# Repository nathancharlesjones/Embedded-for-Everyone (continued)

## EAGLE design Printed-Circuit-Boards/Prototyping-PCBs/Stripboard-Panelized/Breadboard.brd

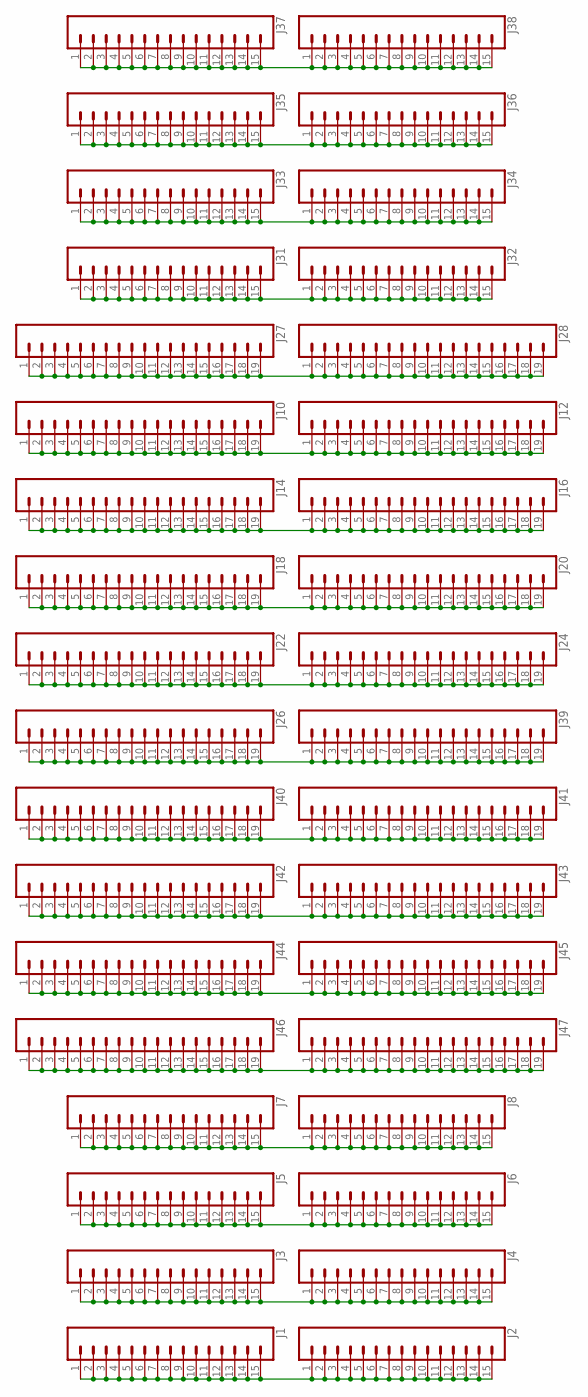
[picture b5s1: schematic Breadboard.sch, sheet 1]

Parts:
J1, J2, J3, J4, J5, J6, J7, J8, J31, J32, J33, J34, J35, J36, J37, J38: CONN_15; 1X15
J10, J12, J14, J16, J18, J20, J22, J24, J26, J27, J28, J39, J40, J41, J42, J43, J44, J45, J46, J47: CONN_19; 1X19

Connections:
unnamed: J37.1, J37.2, J37.3, J37.4, J37.5, J37.6, J37.7, J37.8, J37.9, J37.10, J37.11, J37.12, J37.13, J37.14, J37.15, J38.1, J38.2, J38.3, J38.4, J38.5, J38.6, J38.7, J38.8, J38.9, J38.10, J38.11, J38.12, J38.13, J38.14, J38.15
unnamed: J35.1, J35.2, J35.3, J35.4, J35.5, J35.6, J35.7, J35.8, J35.9, J35.10, J35.11, J35.12, J35.13, J35.14, J35.15, J36.1, J36.2, J36.3, J36.4, J36.5, J36.6, J36.7, J36.8, J36.9, J36.10, J36.11, J36.12, J36.13, J36.14, J36.15
unnamed: J33.1, J33.2, J33.3, J33.4, J33.5, J33.6, J33.7, J33.8, J33.9, J33.10, J33.11, J33.12, J33.13, J33.14, J33.15, J34.1, J34.2, J34.3, J34.4, J34.5, J34.6, J34.7, J34.8, J34.9, J34.10, J34.11, J34.12, J34.13, J34.14, J34.15
unnamed: J31.1, J31.2, J31.3, J31.4, J31.5, J31.6, J31.7, J31.8, J31.9, J31.10, J31.11, J31.12, J31.13, J31.14, J31.15, J32.1, J32.2, J32.3, J32.4, J32.5, J32.6, J32.7, J32.8, J32.9, J32.10, J32.11, J32.12, J32.13, J32.14, J32.15
unnamed: J27.1, J27.2, J27.3, J27.4, J27.5, J27.6, J27.7, J27.8, J27.9, J27.10, J27.11, J27.12, J27.13, J27.14, J27.15, J27.16, J27.17, J27.18, J27.19, J28.1, J28.2, J28.3, J28.4, J28.5, J28.6, J28.7, J28.8, J28.9, J28.10, J28.11, J28.12, J28.13, J28.14, J28.15, J28.16, J28.17, J28.18, J28.19
unnamed: J10.1, J10.2, J10.3, J10.4, J10.5, J10.6, J10.7, J10.8, J10.9, J10.10, J10.11, J10.12, J10.13, J10.14, J10.15, J10.16, J10.17, J10.18, J10.19, J12.1, J12.2, J12.3, J12.4, J12.5, J12.6, J12.7, J12.8, J12.9, J12.10, J12.11, J12.12, J12.13, J12.14, J12.15, J12.16, J12.17, J12.18, J12.19
unnamed: J14.1, J14.2, J14.3, J14.4, J14.5, J14.6, J14.7, J14.8, J14.9, J14.10, J14.11, J14.12, J14.13, J14.14, J14.15, J14.16, J14.17, J14.18, J14.19, J16.1, J16.2, J16.3, J16.4, J16.5, J16.6, J16.7, J16.8, J16.9, J16.10, J16.11, J16.12, J16.13, J16.14, J16.15, J16.16, J16.17, J16.18, J16.19
unnamed: J18.1, J18.2, J18.3, J18.4, J18.5, J18.6, J18.7, J18.8, J18.9, J18.10, J18.11, J18.12, J18.13, J18.14, J18.15, J18.16, J18.17, J18.18, J18.19, J20.1, J20.2, J20.3, J20.4, J20.5, J20.6, J20.7, J20.8, J20.9, J20.10, J20.11, J20.12, J20.13, J20.14, J20.15, J20.16, J20.17, J20.18, J20.19
unnamed: J22.1, J22.2, J22.3, J22.4, J22.5, J22.6, J22.7, J22.8, J22.9, J22.10, J22.11, J22.12, J22.13, J22.14, J22.15, J22.16, J22.17, J22.18, J22.19, J24.1, J24.2, J24.3, J24.4, J24.5, J24.6, J24.7, J24.8, J24.9, J24.10, J24.11, J24.12, J24.13, J24.14, J24.15, J24.16, J24.17, J24.18, J24.19
unnamed: J26.1, J26.2, J26.3, J26.4, J26.5, J26.6, J26.7, J26.8, J26.9, J26.10, J26.11, J26.12, J26.13, J26.14, J26.15, J26.16, J26.17, J26.18, J26.19, J39.1, J39.2, J39.3, J39.4, J39.5, J39.6, J39.7, J39.8, J39.9, J39.10, J39.11, J39.12, J39.13, J39.14, J39.15, J39.16, J39.17, J39.18, J39.19
unnamed: J40.1, J40.2, J40.3, J40.4, J40.5, J40.6, J40.7, J40.8, J40.9, J40.10, J40.11, J40.12, J40.13, J40.14, J40.15, J40.16, J40.17, J40.18, J40.19, J41.1, J41.2, J41.3, J41.4, J41.5, J41.6, J41.7, J41.8, J41.9, J41.10, J41.11, J41.12, J41.13, J41.14, J41.15, J41.16, J41.17, J41.18, J41.19
unnamed: J42.1, J42.2, J42.3, J42.4, J42.5, J42.6, J42.7, J42.8, J42.9, J42.10, J42.11, J42.12, J42.13, J42.14, J42.15, J42.16, J42.17, J42.18, J42.19, J43.1, J43.2, J43.3, J43.4, J43.5, J43.6, J43.7, J43.8, J43.9, J43.10, J43.11, J43.12, J43.13, J43.14, J43.15, J43.16, J43.17, J43.18, J43.19
unnamed: J44.1, J44.2, J44.3, J44.4, J44.5, J44.6, J44.7, J44.8, J44.9, J44.10, J44.11, J44.12, J44.13, J44.14, J44.15, J44.16, J44.17, J44.18, J44.19, J45.1, J45.2, J45.3, J45.4, J45.5, J45.6, J45.7, J45.8, J45.9, J45.10, J45.11, J45.12, J45.13, J45.14, J45.15, J45.16, J45.17, J45.18, J45.19
unnamed: J46.1, J46.2, J46.3, J46.4, J46.5, J46.6, J46.7, J46.8, J46.9, J46.10, J46.11, J46.12, J46.13, J46.14, J46.15, J46.16, J46.17, J46.18, J46.19, J47.1, J47.2, J47.3, J47.4, J47.5, J47.6, J47.7, J47.8, J47.9, J47.10, J47.11, J47.12, J47.13, J47.14, J47.15, J47.16, J47.17, J47.18, J47.19
unnamed: J7.1, J7.2, J7.3, J7.4, J7.5, J7.6, J7.7, J7.8, J7.9, J7.10, J7.11, J7.12, J7.13, J7.14, J7.15, J8.1, J8.2, J8.3, J8.4, J8.5, J8.6, J8.7, J8.8, J8.9, J8.10, J8.11, J8.12, J8.13, J8.14, J8.15
unnamed: J5.1, J5.2, J5.3, J5.4, J5.5, J5.6, J5.7, J5.8, J5.9, J5.10, J5.11, J5.12, J5.13, J5.14, J5.15, J6.1, J6.2, J6.3, J6.4, J6.5, J6.6, J6.7, J6.8, J6.9, J6.10, J6.11, J6.12, J6.13, J6.14, J6.15
unnamed: J3.1, J3.2, J3.3, J3.4, J3.5, J3.6, J3.7, J3.8, J3.9, J3.10, J3.11, J3.12, J3.13, J3.14, J3.15, J4.1, J4.2, J4.3, J4.4, J4.5, J4.6, J4.7, J4.8, J4.9, J4.10, J4.11, J4.12, J4.13, J4.14, J4.15
unnamed: J1.1, J1.2, J1.3, J1.4, J1.5, J1.6, J1.7, J1.8, J1.9, J1.10, J1.11, J1.12, J1.13, J1.14, J1.15, J2.1, J2.2, J2.3, J2.4, J2.5, J2.6, J2.7, J2.8, J2.9, J2.10, J2.11, J2.12, J2.13, J2.14, J2.15

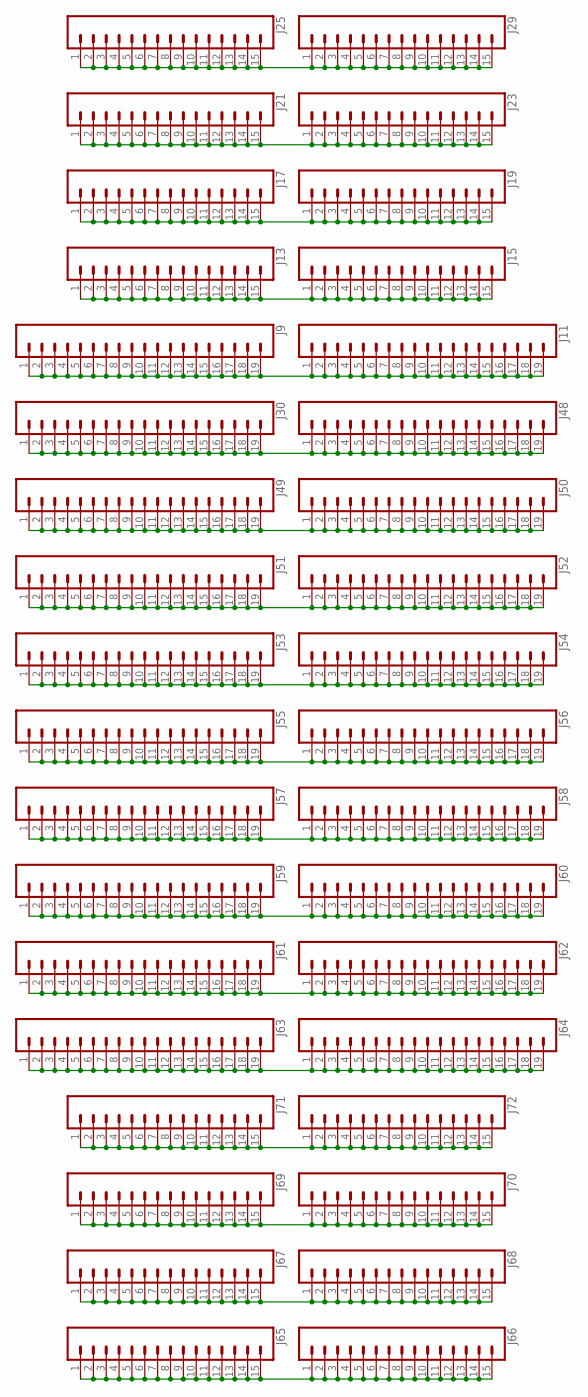
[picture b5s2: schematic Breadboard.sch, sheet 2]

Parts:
J9, J11, J30, J48, J49, J50, J51, J52, J53, J54, J55, J56, J57, J58, J59, J60, J61, J62, J63, J64: CONN_19; 1X19
J13, J15, J17, J19, J21, J23, J25, J29, J65, J66, J67, J68, J69, J70, J71, J72: CONN_15; 1X15

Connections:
unnamed: J25.1, J25.2, J25.3, J25.4, J25.5, J25.6, J25.7, J25.8, J25.9, J25.10, J25.11, J25.12, J25.13, J25.14, J25.15, J29.1, J29.2, J29.3, J29.4, J29.5, J29.6, J29.7, J29.8, J29.9, J29.10, J29.11, J29.12, J29.13, J29.14, J29.15
unnamed: J21.1, J21.2, J21.3, J21.4, J21.5, J21.6, J21.7, J21.8, J21.9, J21.10, J21.11, J21.12, J21.13, J21.14, J21.15, J23.1, J23.2, J23.3, J23.4, J23.5, J23.6, J23.7, J23.8, J23.9, J23.10, J23.11, J23.12, J23.13, J23.14, J23.15
unnamed: J17.1, J17.2, J17.3, J17.4, J17.5, J17.6, J17.7, J17.8, J17.9, J17.10, J17.11, J17.12, J17.13, J17.14, J17.15, J19.1, J19.2, J19.3, J19.4, J19.5, J19.6, J19.7, J19.8, J19.9, J19.10, J19.11, J19.12, J19.13, J19.14, J19.15
unnamed: J13.1, J13.2, J13.3, J13.4, J13.5, J13.6, J13.7, J13.8, J13.9, J13.10, J13.11, J13.12, J13.13, J13.14, J13.15, J15.1, J15.2, J15.3, J15.4, J15.5, J15.6, J15.7, J15.8, J15.9, J15.10, J15.11, J15.12, J15.13, J15.14, J15.15
unnamed: J9.1, J9.2, J9.3, J9.4, J9.5, J9.6, J9.7, J9.8, J9.9, J9.10, J9.11, J9.12, J9.13, J9.14, J9.15, J9.16, J9.17, J9.18, J9.19, J11.1, J11.2, J11.3, J11.4, J11.5, J11.6, J11.7, J11.8, J11.9, J11.10, J11.11, J11.12, J11.13, J11.14, J11.15, J11.16, J11.17, J11.18, J11.19
unnamed: J30.1, J30.2, J30.3, J30.4, J30.5, J30.6, J30.7, J30.8, J30.9, J30.10, J30.11, J30.12, J30.13, J30.14, J30.15, J30.16, J30.17, J30.18, J30.19, J48.1, J48.2, J48.3, J48.4, J48.5, J48.6, J48.7, J48.8, J48.9, J48.10, J48.11, J48.12, J48.13, J48.14, J48.15, J48.16, J48.17, J48.18, J48.19
unnamed: J49.1, J49.2, J49.3, J49.4, J49.5, J49.6, J49.7, J49.8, J49.9, J49.10, J49.11, J49.12, J49.13, J49.14, J49.15, J49.16, J49.17, J49.18, J49.19, J50.1, J50.2, J50.3, J50.4, J50.5, J50.6, J50.7, J50.8, J50.9, J50.10, J50.11, J50.12, J50.13, J50.14, J50.15, J50.16, J50.17, J50.18, J50.19
unnamed: J51.1, J51.2, J51.3, J51.4, J51.5, J51.6, J51.7, J51.8, J51.9, J51.10, J51.11, J51.12, J51.13, J51.14, J51.15, J51.16, J51.17, J51.18, J51.19, J52.1, J52.2, J52.3, J52.4, J52.5, J52.6, J52.7, J52.8, J52.9, J52.10, J52.11, J52.12, J52.13, J52.14, J52.15, J52.16, J52.17, J52.18, J52.19
unnamed: J53.1, J53.2, J53.3, J53.4, J53.5, J53.6, J53.7, J53.8, J53.9, J53.10, J53.11, J53.12, J53.13, J53.14, J53.15, J53.16, J53.17, J53.18, J53.19, J54.1, J54.2, J54.3, J54.4, J54.5, J54.6, J54.7, J54.8, J54.9, J54.10, J54.11, J54.12, J54.13, J54.14, J54.15, J54.16, J54.17, J54.18, J54.19
unnamed: J55.1, J55.2, J55.3, J55.4, J55.5, J55.6, J55.7, J55.8, J55.9, J55.10, J55.11, J55.12, J55.13, J55.14, J55.15, J55.16, J55.17, J55.18, J55.19, J56.1, J56.2, J56.3, J56.4, J56.5, J56.6, J56.7, J56.8, J56.9, J56.10, J56.11, J56.12, J56.13, J56.14, J56.15, J56.16, J56.17, J56.18, J56.19
unnamed: J57.1, J57.2, J57.3, J57.4, J57.5, J57.6, J57.7, J57.8, J57.9, J57.10, J57.11, J57.12, J57.13, J57.14, J57.15, J57.16, J57.17, J57.18, J57.19, J58.1, J58.2, J58.3, J58.4, J58.5, J58.6, J58.7, J58.8, J58.9, J58.10, J58.11, J58.12, J58.13, J58.14, J58.15, J58.16, J58.17, J58.18, J58.19
unnamed: J59.1, J59.2, J59.3, J59.4, J59.5, J59.6, J59.7, J59.8, J59.9, J59.10, J59.11, J59.12, J59.13, J59.14, J59.15, J59.16, J59.17, J59.18, J59.19, J60.1, J60.2, J60.3, J60.4, J60.5, J60.6, J60.7, J60.8, J60.9, J60.10, J60.11, J60.12, J60.13, J60.14, J60.15, J60.16, J60.17, J60.18, J60.19
unnamed: J61.1, J61.2, J61.3, J61.4, J61.5, J61.6, J61.7, J61.8, J61.9, J61.10, J61.11, J61.12, J61.13, J61.14, J61.15, J61.16, J61.17, J61.18, J61.19, J62.1, J62.2, J62.3, J62.4, J62.5, J62.6, J62.7, J62.8, J62.9, J62.10, J62.11, J62.12, J62.13, J62.14, J62.15, J62.16, J62.17, J62.18, J62.19
unnamed: J63.1, J63.2, J63.3, J63.4, J63.5, J63.6, J63.7, J63.8, J63.9, J63.10, J63.11, J63.12, J63.13, J63.14, J63.15, J63.16, J63.17, J63.18, J63.19, J64.1, J64.2, J64.3, J64.4, J64.5, J64.6, J64.7, J64.8, J64.9, J64.10, J64.11, J64.12, J64.13, J64.14, J64.15, J64.16, J64.17, J64.18, J64.19
unnamed: J71.1, J71.2, J71.3, J71.4, J71.5, J71.6, J71.7, J71.8, J71.9, J71.10, J71.11, J71.12, J71.13, J71.14, J71.15, J72.1, J72.2, J72.3, J72.4, J72.5, J72.6, J72.7, J72.8, J72.9, J72.10, J72.11, J72.12, J72.13, J72.14, J72.15
unnamed: J69.1, J69.2, J69.3, J69.4, J69.5, J69.6, J69.7, J69.8, J69.9, J69.10, J69.11, J69.12, J69.13, J69.14, J69.15, J70.1, J70.2, J70.3, J70.4, J70.5, J70.6, J70.7, J70.8, J70.9, J70.10, J70.11, J70.12, J70.13, J70.14, J70.15
unnamed: J67.1, J67.2, J67.3, J67.4, J67.5, J67.6, J67.7, J67.8, J67.9, J67.10, J67.11, J67.12, J67.13, J67.14, J67.15, J68.1, J68.2, J68.3, J68.4, J68.5, J68.6, J68.7, J68.8, J68.9, J68.10, J68.11, J68.12, J68.13, J68.14, J68.15
unnamed: J65.1, J65.2, J65.3, J65.4, J65.5, J65.6, J65.7, J65.8, J65.9, J65.10, J65.11, J65.12, J65.13, J65.14, J65.15, J66.1, J66.2, J66.3, J66.4, J66.5, J66.6, J66.7, J66.8, J66.9, J66.10, J66.11, J66.12, J66.13, J66.14, J66.15

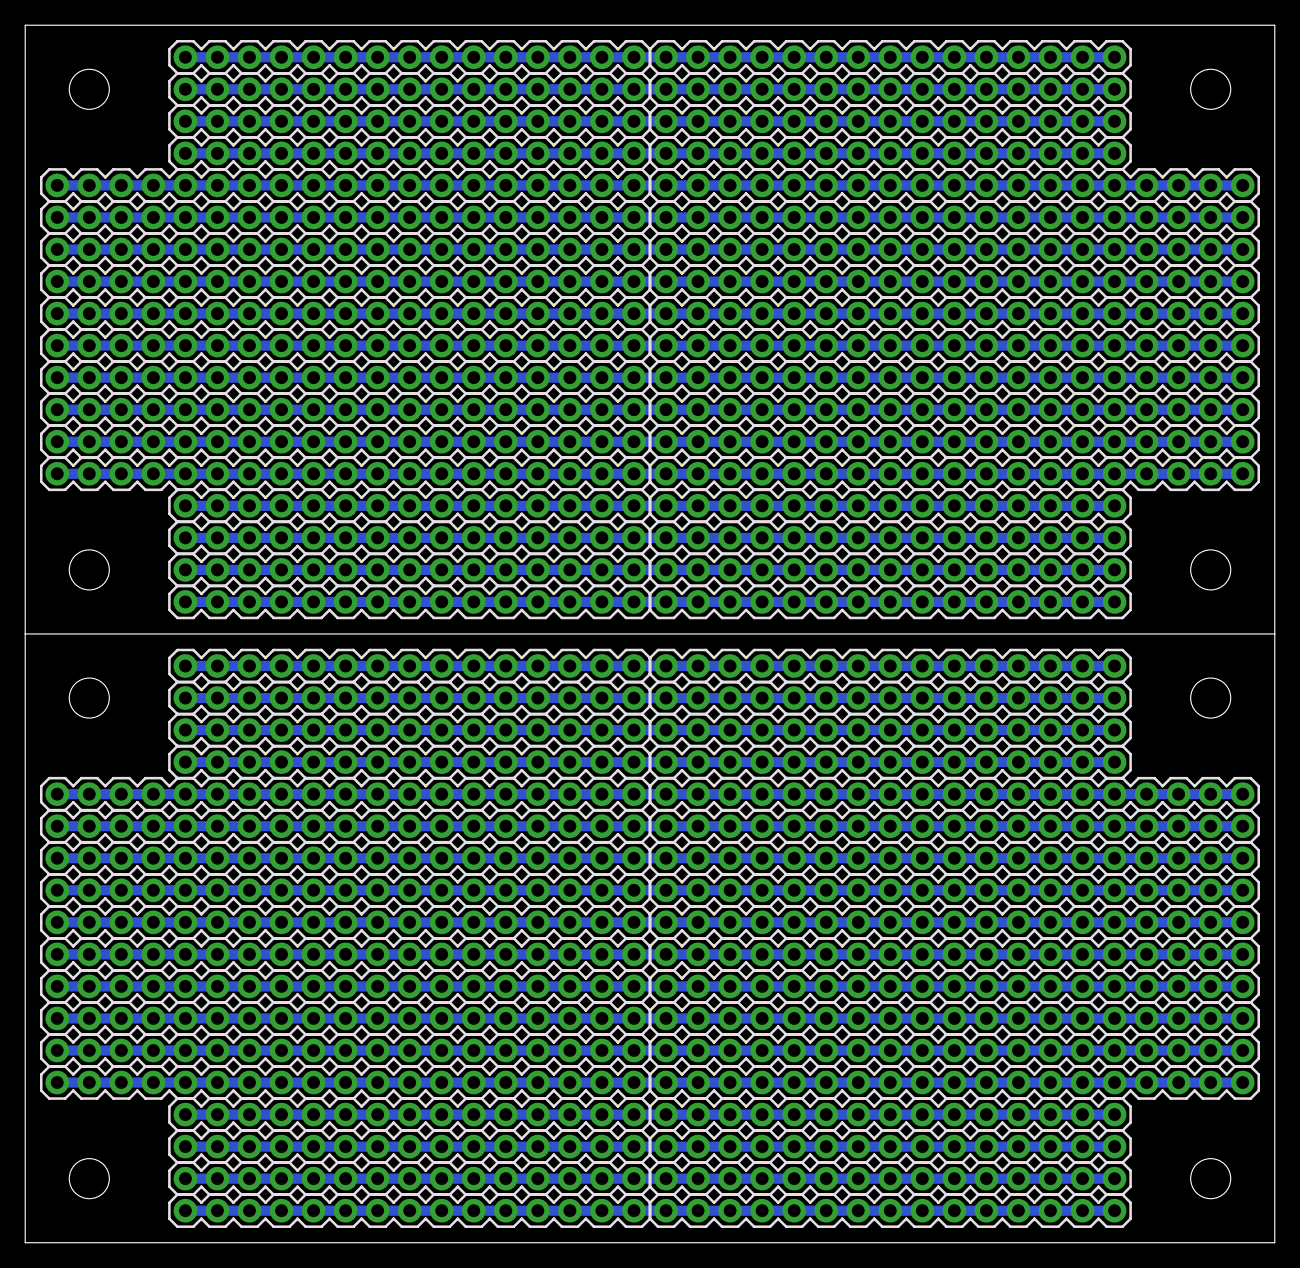
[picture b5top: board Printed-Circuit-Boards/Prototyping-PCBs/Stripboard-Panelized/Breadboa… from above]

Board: 2 copper layers, 99.1 x 96.5 mm, 72 parts (0 on the bottom side), 36 nets.

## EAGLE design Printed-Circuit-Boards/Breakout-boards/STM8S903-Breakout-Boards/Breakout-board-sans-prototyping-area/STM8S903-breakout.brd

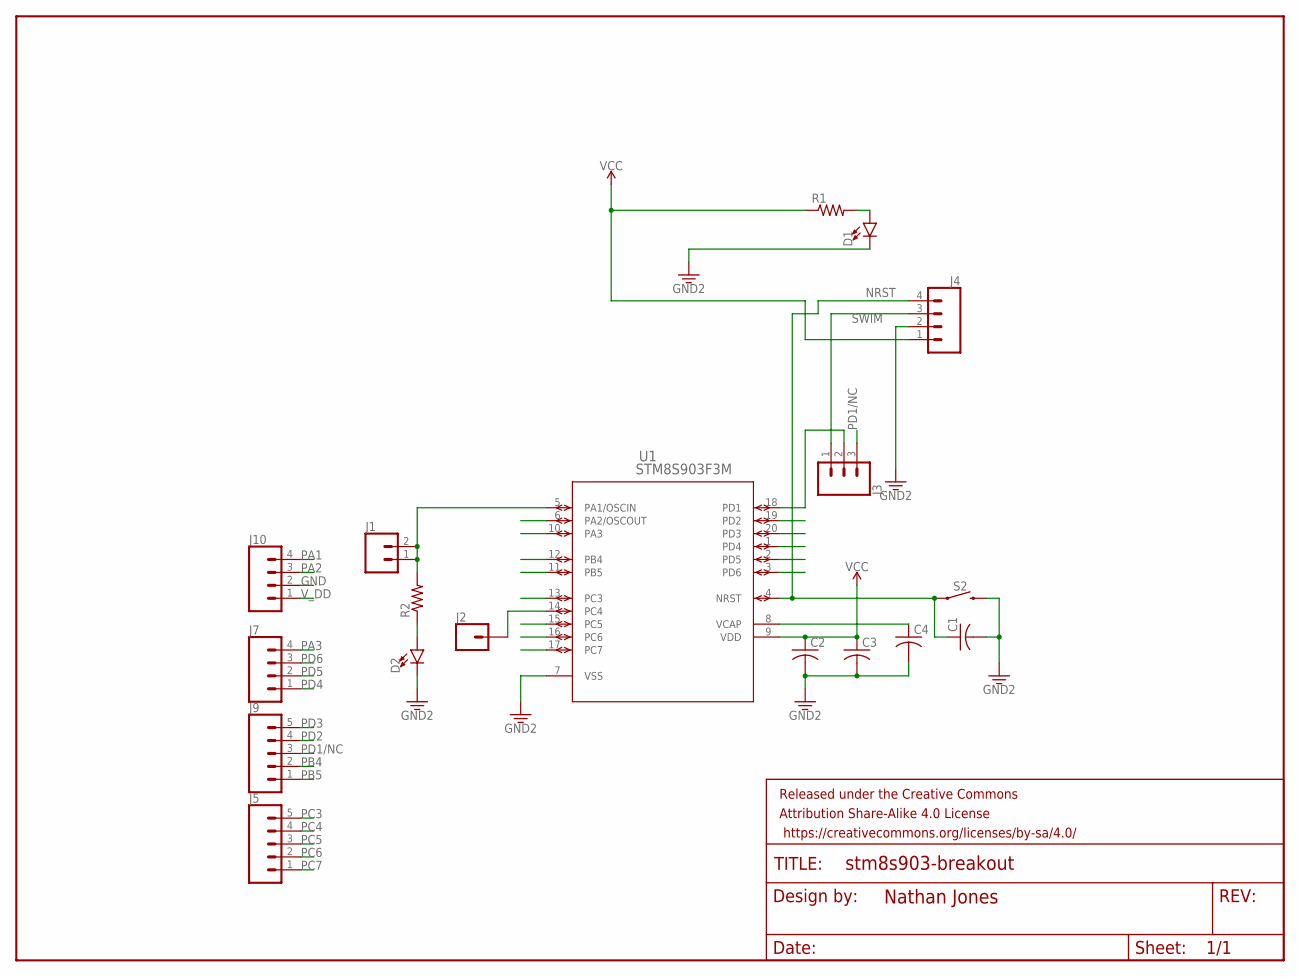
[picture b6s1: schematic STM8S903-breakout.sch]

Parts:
C1, C2, C3, C4: C-USC1206; C1206
D1, D2: LED1206; LED-1206
FRAME1: FRAME-LETTERNO_PACKAGE; DUMMY
J1: CONN_02PTH3; 1X02_LONGPADS
J2: CONN_01PTH_LONGPAD; 1X01_LONGPAD
J3: CONN_03LONGPADS; 1X03_LONGPADS
J4, J7, J10: CONN_04LONGPADS; 1X04_LONGPADS
J5, J9: CONN_05PTH_LONGPADS; 1X05_LONGPADS
R1, R2: R-US_R1206; R1206
S2: MOMENTARY-SWITCH-SPST-SMD-4.5MM; TACTILE_SWITCH_SMD_4.5MM
U1: STM8S903F3M; SO-20

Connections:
GND: C1.2, C2.2, C3.2, C4.2, D1.C, D2.C, J4.2, J10.2, S2.1 (2), S2.4 (2), U1.7 (VSS)
unnamed: D1.A, R1.2
unnamed: D2.A, R2.1
NRST: C1.1, J4.4, S2.2 (1), S2.3 (1), U1.4 (NRST)
PA1: J1.1, J1.2, J10.4, R2.2, U1.5 (PA1/OSCIN)
PA2: J10.3, U1.6 (PA2/OSCOUT)
PA3: J7.4, U1.10 (PA3)
PB4: J9.2, U1.12 (PB4)
PB5: J9.1, U1.11 (PB5)
PC3: J5.5, U1.13 (PC3)
PC4: J2.1, J5.4, U1.14 (PC4)
PC5: J5.3, U1.15 (PC5)
PC6: J5.2, U1.16 (PC6)
PC7: J5.1, U1.17 (PC7)
PD1: J3.2, U1.18 (PD1)
PD1/NC: J3.3, J9.3
PD2: J9.4, U1.19 (PD2)
PD3: J9.5, U1.20 (PD3)
PD4: J7.1, U1.1 (PD4)
PD5: J7.2, U1.2 (PD5)
PD6: J7.3, U1.3 (PD6)
SWIM: J3.1, J4.3
V_CAP: C4.1, U1.8 (VCAP)
V_DD: C2.1, C3.1, J4.1, J10.1, R1.1, U1.9 (VDD)

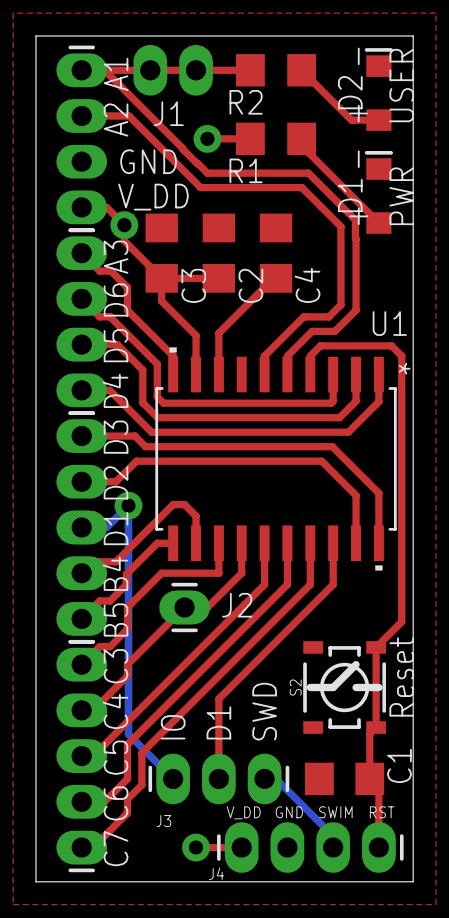
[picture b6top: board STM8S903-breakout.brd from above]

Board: 2 copper layers, 21.0 x 47.0 mm, 19 parts (0 on the bottom side), 24 nets.

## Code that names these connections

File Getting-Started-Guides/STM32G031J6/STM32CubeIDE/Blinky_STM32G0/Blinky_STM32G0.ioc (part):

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Mcu.Name=STM32G031J(4-6)Mx
Mcu.Package=SO8N
Mcu.UserName=STM32G031J6Mx
PA12\ [PA10].GPIOParameters=GPIO_Label
PA12\ [PA10].GPIO_Label=LED1
PA12\ [PA10].Signal=GPIO_Output
PA13.Mode=Serial_Wire
PA13.Signal=SYS_SWDIO
PA14-BOOT0.Mode=Serial_Wire
PA14-BOOT0.Signal=SYS_SWCLK
RCC.HSE_VALUE=8000000
RCC.SYSCLKFreq_VALUE=64000000
RCC.SYSCLKSource=RCC_SYSCLKSOURCE_PLLCLK
board=custom

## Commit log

2019-11-25 Added breadboard-style PCBs built using Eagle. One is a single board and one is panelized.
2019-11-25 Added two breakout boards sans prototyping area: the STM32G031J6M6 and the STM8S903F3M6.
2020-03-05 Added toolchain images to Supporting-documents.
2020-03-05 Added 'Device Support.htm' to Supporting-documents.
2020-03-06 Added PDF getting started guides for MSP430, PIC16/PIC18/dsPIC33, XMC1100, and STM32G0.
2020-03-06 Updated PCB files.
2020-03-06 End of day check to make sure all changes were pushed.
2020-03-11 Added MPLAB SNAP-compatible list of DIP MCUs.
2020-03-11 Squashed 'Printed-Circuit-Boards/Breakout-boards/STM32F030F4P6-Breakout-Boards/Single/' content from commit 92c8002
    git-subtree-dir: Printed-Circuit-Boards/Breakout-boards/STM32F030F4P6-Breakout-Boards/Single
    git-subtree-split: 92c8002656f7f19e60e936bdac4dc6e0f8158771
2020-03-11 Removed STM32F030F4P6 subtree.
2020-03-11 Added link to STM32F030F4P6 repo (hopefully).
2020-03-11 Removed dead STM32G0 files.
2020-03-11 Added link to STM32G0 repo.
2020-03-11 Removed STM8S903 breakout board folder.
2020-03-11 Added links to prototyping PCBs.
2020-03-11 Added Eagle design rule files.
2020-03-12 Updated toolchain images.
2020-03-12 Testing PDF.
2020-03-12 Updated STM32F030F4P6 breakout board submodule.
2020-03-12 Updated STM32F030F4P6 submodule (hopefully).
2020-03-12 Updating submodule STM32G0.
2020-03-12 Updating submodule STM32F0.
2020-03-12 Updating submodule Breadboard-Single.
2020-03-12 Updating submodule Stripboard-Single.
2020-03-18 Added project files for LPC845, command line and Segger + J-Link.
2020-03-20 Added command line files for LPC845-BRK.
2020-03-20 Added project files for NXP MCUXpresso.
2020-03-25 Added Compatible Toolchains.
2020-03-25 Added PDF Getting Started guide for the LPC845.
2020-03-26 Added files for CC Studio.
2020-03-26 Added programming project files for PIC16 and dsPIC33.
2020-03-27 Added project files for MSP430, PIC16, dsPIC33, and XMC1100.
2020-03-27 Added DAVE project files for XMC1100.
2020-03-27 Added STM32CubeIDE and command line project files for STM32G0.
2020-03-27 Removed duplicate project folders for STM32G0. Added Keil MDK-Arm project files for STM32G0.
2020-03-27 Updated Build-minimal-for-LPC845.sh.
2020-03-27 Updated getting started guides and Compatible Toolchains files.
2020-03-30 Updated PCB submodules.
2020-03-30 Added individual getting started guides as submodules.
2020-03-30 Updated README.
2020-03-31 Updated bootloader image.
2020-03-31 Updated README for Eagle design rule files.
2020-04-21 Added graphics from Ryan Jones.
2020-04-25 Updated sub-modules that had new Getting Started guides.
2020-05-11 Added final paper. Added and updated graphics.
2020-05-11 Updated root README to include Embedded for Everyone PDF in the file structure.
